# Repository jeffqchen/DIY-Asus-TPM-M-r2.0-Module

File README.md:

# DIY ASUS TPM-M R2.0 Module

It's kinda hard to find those TPM modules that no one knew they needed - UNTIL Windows 11 happened. So here's one in case you need it.

There are many variants, so please use this as a reference to create your own.

--------

## Adapt to Asrock Motherboards

This module can also work on Asrock motherboards if you use [THIS](https://github.com/jeffqchen/DIY-Asus-TPM-M-r2.0-Module/tree/main/Asus%20To%20Asrock/KiCAD) adapter!

--------

## Parts

SLB9665TT20 TPM Chip:

-  https://www.ebay.com/itm/313526673758

2 mm pitch double row right angle pin header -   Choose the 2x7 option
-  https://www.aliexpress.com/item/32887332295.html

4x 100nF 6.3V 0603 SMD capacitors

2x 10K Ohm 0603 SMD resistors

PCB:
-   https://oshpark.com/shared_projects/pVqwq0NS

Note: You do NOT have to follow the links I used. The specs are pretty laid out so you can source your own parts if you prefer.

3D Printed Shell (Optional)
  - Print with the text facing upwards
  - Suggested layer height: 0.16mm.
  - Suggested line width: 0.35mm.
  - Uses two 6mm M2 screw and nut.
--------

## Assembly

You have to know how to solder VERY well. Experience in soldering TSSOP and SMD components is required.

Note the pin header should be keyed. You can cut a piece of the compatible pin and stuff it into the hole on the bottom row, the 3rd one from the right.

Note: if you are an amateur on soldering, this might not be a bad project to learn how to solder, since everything is quite affordable. Learn how to pre-tin SMD pads for caps and resistor, how to tack a chip in place, and then drag solder alone one side, then the other. We all have to start from somewhere.

--------

## Installation

Jam it onto your motherboard with power turned OFF (I don't have to teach you the basics, right?) For my motherboard, once booted into the BIOS, the chip is automatically recognized and ready to go. Windows 10 also recognized it without any fuss.

-------

## Updating TPM Chip Firmware

The firmware version on the chip might be quite out-dated and requires an update to work properly with Windows. Please refer to the following guides on how to update the firmware on your TPM chip:
- https://qzhou.dev/updating-a-vulnerable-tpm
- https://silvenga.com/upgrading-firmware-infineon-tpm/

Note: It is possible that your chips might come with a rare firmware version and no update could be found. You might have to find a different seller and try your luck if that's the case.

--------

## Reference

SLB9665TT20 Datasheet:
- https://www.infineon.com/dgdl/Infineon-data-sheet-SLB9665_2.0_Rev1.2-DS-v01_02-EN.pdf?fileId=5546d462689a790c016929d1d3054feb

--------
Shield: [![CC BY-SA 4.0][cc-by-sa-shield]][cc-by-sa]

This work is licensed under a
[Creative Commons Attribution-ShareAlike 4.0 International License][cc-by-sa].

[![CC BY-SA 4.0][cc-by-sa-image]][cc-by-sa]

[cc-by-sa]: http://creativecommons.org/licenses/by-sa/4.0/
[cc-by-sa-image]: https://licensebuttons.net/l/by-sa/4.0/88x31.png
[cc-by-sa-shield]: https://img.shields.io/badge/License-CC%20BY--SA%204.0-lightgrey.svg

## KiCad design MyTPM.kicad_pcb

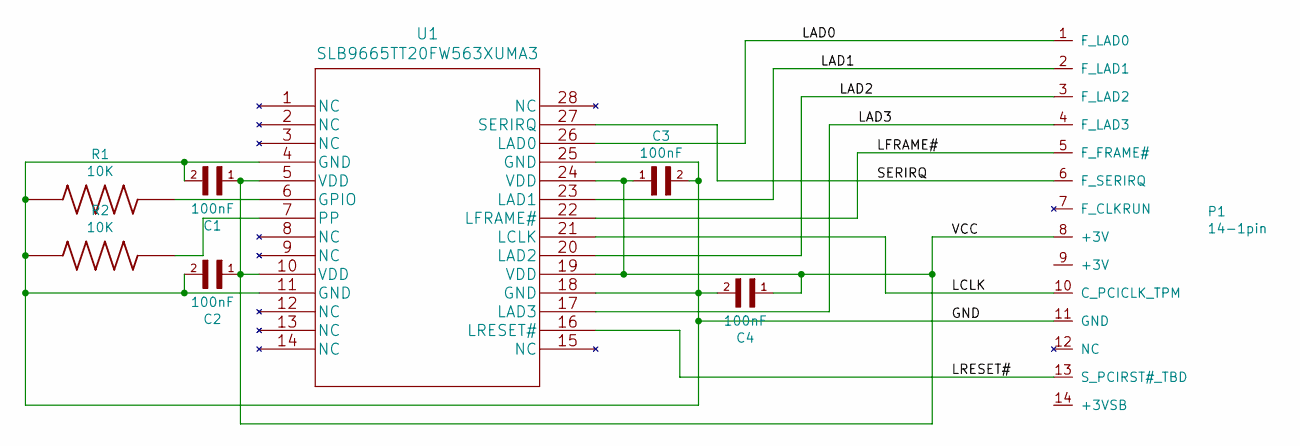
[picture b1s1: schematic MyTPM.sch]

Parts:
C1, C2, C3, C4: 100nF; CAPC1608X87N
P1: 14-1pin; 14-1Pin
R1, R2: 10K; RESC1608X55N
U1: SLB9665TT20FW563XUMA3; SLB9665TT20

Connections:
/GND: C1.2, C2.2, C3.2, C4.2, P1.11 (GND), R1.1, R2.1, U1.4 (GND), U1.11 (GND), U1.18 (GND), U1.25 (GND)
/LAD0: P1.1 (F_LAD0), U1.26 (LAD0)
/LAD1: P1.2 (F_LAD1), U1.23 (LAD1)
/LAD2: P1.3 (F_LAD2), U1.20 (LAD2)
/LAD3: P1.4 (F_LAD3), U1.17 (LAD3)
/LCLK: P1.10 (C_PCICLK_TPM), U1.21 (LCLK)
/LFRAME#: P1.5 (F_FRAME#), U1.22 (LFRAME#)
/LRESET#: P1.13 (S_PCIRST#_TBD), U1.16 (LRESET#)
/SERIRQ: P1.6 (F_SERIRQ), U1.27 (SERIRQ)
/VCC: C1.1, C2.1, C3.1, C4.1, P1.8 (+3V), U1.5 (VDD), U1.10 (VDD), U1.19 (VDD), U1.24 (VDD)
unnamed: R1.2, U1.6 (GPIO)
unnamed: R2.2, U1.7 (PP)

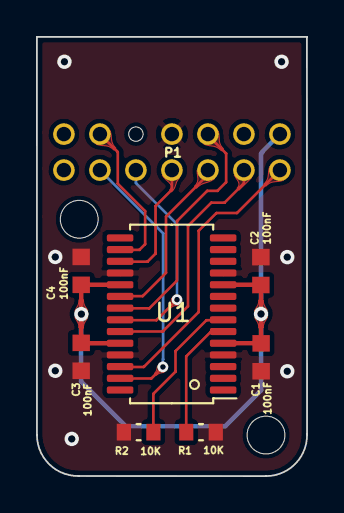
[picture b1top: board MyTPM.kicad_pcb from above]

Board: 2 copper layers, 15.0 x 24.4 mm, 8 parts (1 on the bottom side), 12 nets.

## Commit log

2021-08-09 Add 3D print STL
2021-08-09 Add logoless 3D print
2022-08-09 Add license type
2024-12-01 Asus to Asrock Adapter
